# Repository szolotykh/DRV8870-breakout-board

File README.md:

# DRV8870 Motor Controller

The Motor Controller, powered by Texas Instruments' DRV8870 motor drive, is a robust and efficient solution for running small to medium-sized DC motors. This compact device offers a 3.6V to 18V operating supply voltage range, ensuring compatibility with various power sources. It can efficiently drive a peak current of up to 3.6A, facilitating smooth motor operations even under demanding conditions. Equipped with advanced safety features like overcurrent, thermal, and undervoltage protection, the motor controller ensures your motor's longevity and reliable performance. Whether you're building a robot, an automatic door, or a smart home gadget, this motor controller offers easy integration and optimal performance, bringing your projects to life with precision and power.

## Features

 - PWM control
 - Motor Voltage 6.5V to 45V
 - Logic voltage 3.3V
 - Peak Current 3.6-A
 - 565mΩ Typical RDS(on) (high + low)
 - Dimensions 27 mm x 40 mm
 - Mounting hole diameter 3.2 mm
 - Low-Power Sleep Mode
 - Integrated Current Regulation
 - Overcurrent Protection
 - Thermal Shutdown
 - Automatic Fault Recovery
 - VM Undervoltage Lockout

## Examples

Here are example Arduino sketches that demonstrate how to control a DC motor using the DRV8870 Motor Controller

### PWM Control

```Arduino
// define the motor control pins
int in1Pin = 2;
int in2Pin = 3;

void setup() {
// set the motor control pins as outputs
pinMode(in1Pin, OUTPUT);
pinMode(in2Pin, OUTPUT);

// set the motor speed to half of the maximum
int speed = 127;

// set the direction to forward
digitalWrite(in1Pin, HIGH);
digitalWrite(in2Pin, LOW);

// apply the PWM signal to the EN pin
analogWrite(enPin, speed);
}

void loop() {
// do nothing
}
```

## Resources

- [DRV8870 Datasheet](https://www.ti.com/lit/ds/symlink/drv8870.pdf?ts=1688501994593&ref_url=https%253A%252F%252Fwww.ti.com%252Fproduct%252FDRV8870)

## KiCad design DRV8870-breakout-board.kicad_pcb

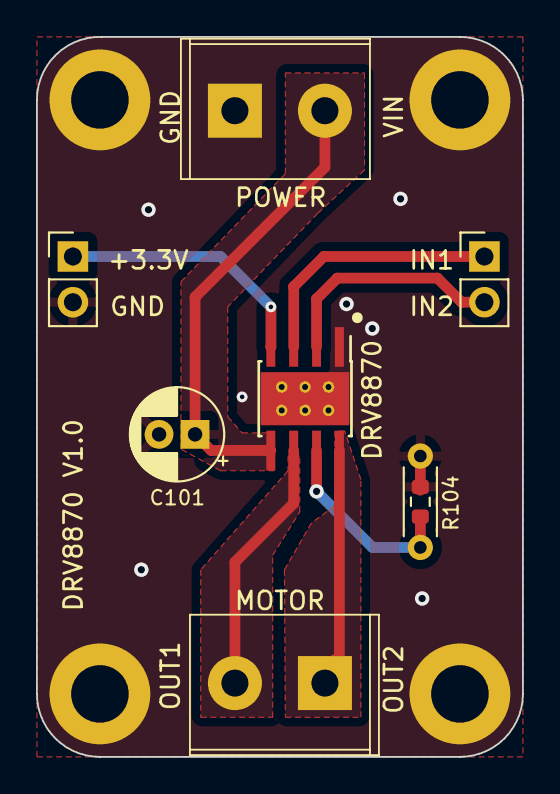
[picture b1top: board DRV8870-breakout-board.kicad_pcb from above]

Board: 2 copper layers, 27.0 x 40.0 mm, 12 parts (0 on the bottom side), 8 nets.

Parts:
C101: 47u; CP_Radial_D5.0mm_P2.00mm
H101, H102, H103, H104: MountingHole; MountingHole_3.2mm_M3_DIN965_Pad
J101, J103: M0_CONN; JILN JL126-50002G01
J102, J104: Conn_01x02_Pin; PinHeader_1x02_P2.54mm_Vertical
R104: 0.15; R_0603_1608Metric
R105: R_Axial_DIN0204_L3.6mm_D1.6mm_P5.08mm_Horizontal
U102: DRV8870DDA; Texas_HTSOP-8-1EP_3.9x4.9mm_P1.27mm_EP2.95x4.9mm_Mask2.4x3.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

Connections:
+3V3: J104.1, U102.4 (VREF)
GND: C101.2, H101.1, H102.1, H103.1, H104.1, J103.1, J104.2, R104.2, R105.2, U102.1 (GND), U102.9 (GND)
IN1: J102.1, U102.3 (IN1)
IN2: J102.2, U102.2 (IN2)
unnamed: R104.1, R105.1, U102.7 (ISEN)
OUT1: J101.2, U102.6 (OUT1)
OUT2: J101.1, U102.8 (OUT2)
VMOTORS: C101.1, J103.2, U102.5 (VM)

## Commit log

2023-06-18 Version 1.0
2023-06-18 Create LICENSE
2023-07-04 Add 3d models and technical drawing
2023-07-05 Update file structure
2023-07-06 Update image
